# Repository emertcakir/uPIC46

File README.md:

# uPIC46
EMC

uPIC46 Development Board

The uPIC46 is a development board designed around the Microchip PIC18F46K22-I/PT microcontroller.  
It is intended for hobbyists, students, and professionals who want a versatile platform for learning, prototyping, and industrial communication testing.

----------------------------------------------------
✨ Features
----------------------------------------------------
- MCU: PIC18F46K22-I/PT (TQFP package)
- Clocking: External crystal oscillator support
- Memory Expansion: Onboard 24LC256 I²C EEPROM
- RTC: DS3231MZ real-time clock
- USB-UART Bridge: For programming and PC communication
- Connectivity:
  * UART, SPI, I²C headers exposed
  * RTS/CTS and other flow-control pins available on headers
  * RS-485 transceiver for half-duplex communication
  * CAN Bus interface via MCP2515 + SN65HVD230
- Reset & Indicators:
  * Reset push button
  * User indicator LEDs
- Headers:
  * Clearly labeled header pins (A1, A2, A3…) with silkscreen reference table on PCB
  * Breakout headers for easy access to MCU I/O pins

----------------------------------------------------
🛠 Hardware Design
----------------------------------------------------
- Compact and user-friendly layout
- Industrial interfaces: CAN and RS-485 included
- Silkscreen pinout table on PCB for quick reference
----------------------------------------------------
📸 Images
----------------------------------------------------

----------------------------------------------------
📜 License
----------------------------------------------------
This project is open-source. You are free to use, modify, and distribute it under the terms of the MIT License.

CRITICAL WARNING: This PCB design is currently an experimental, unverified prototype (AS-IS). I have not yet manufactured or functionally tested this version. Proceeding with production carries a high risk of failure and is undertaken solely at your own risk.

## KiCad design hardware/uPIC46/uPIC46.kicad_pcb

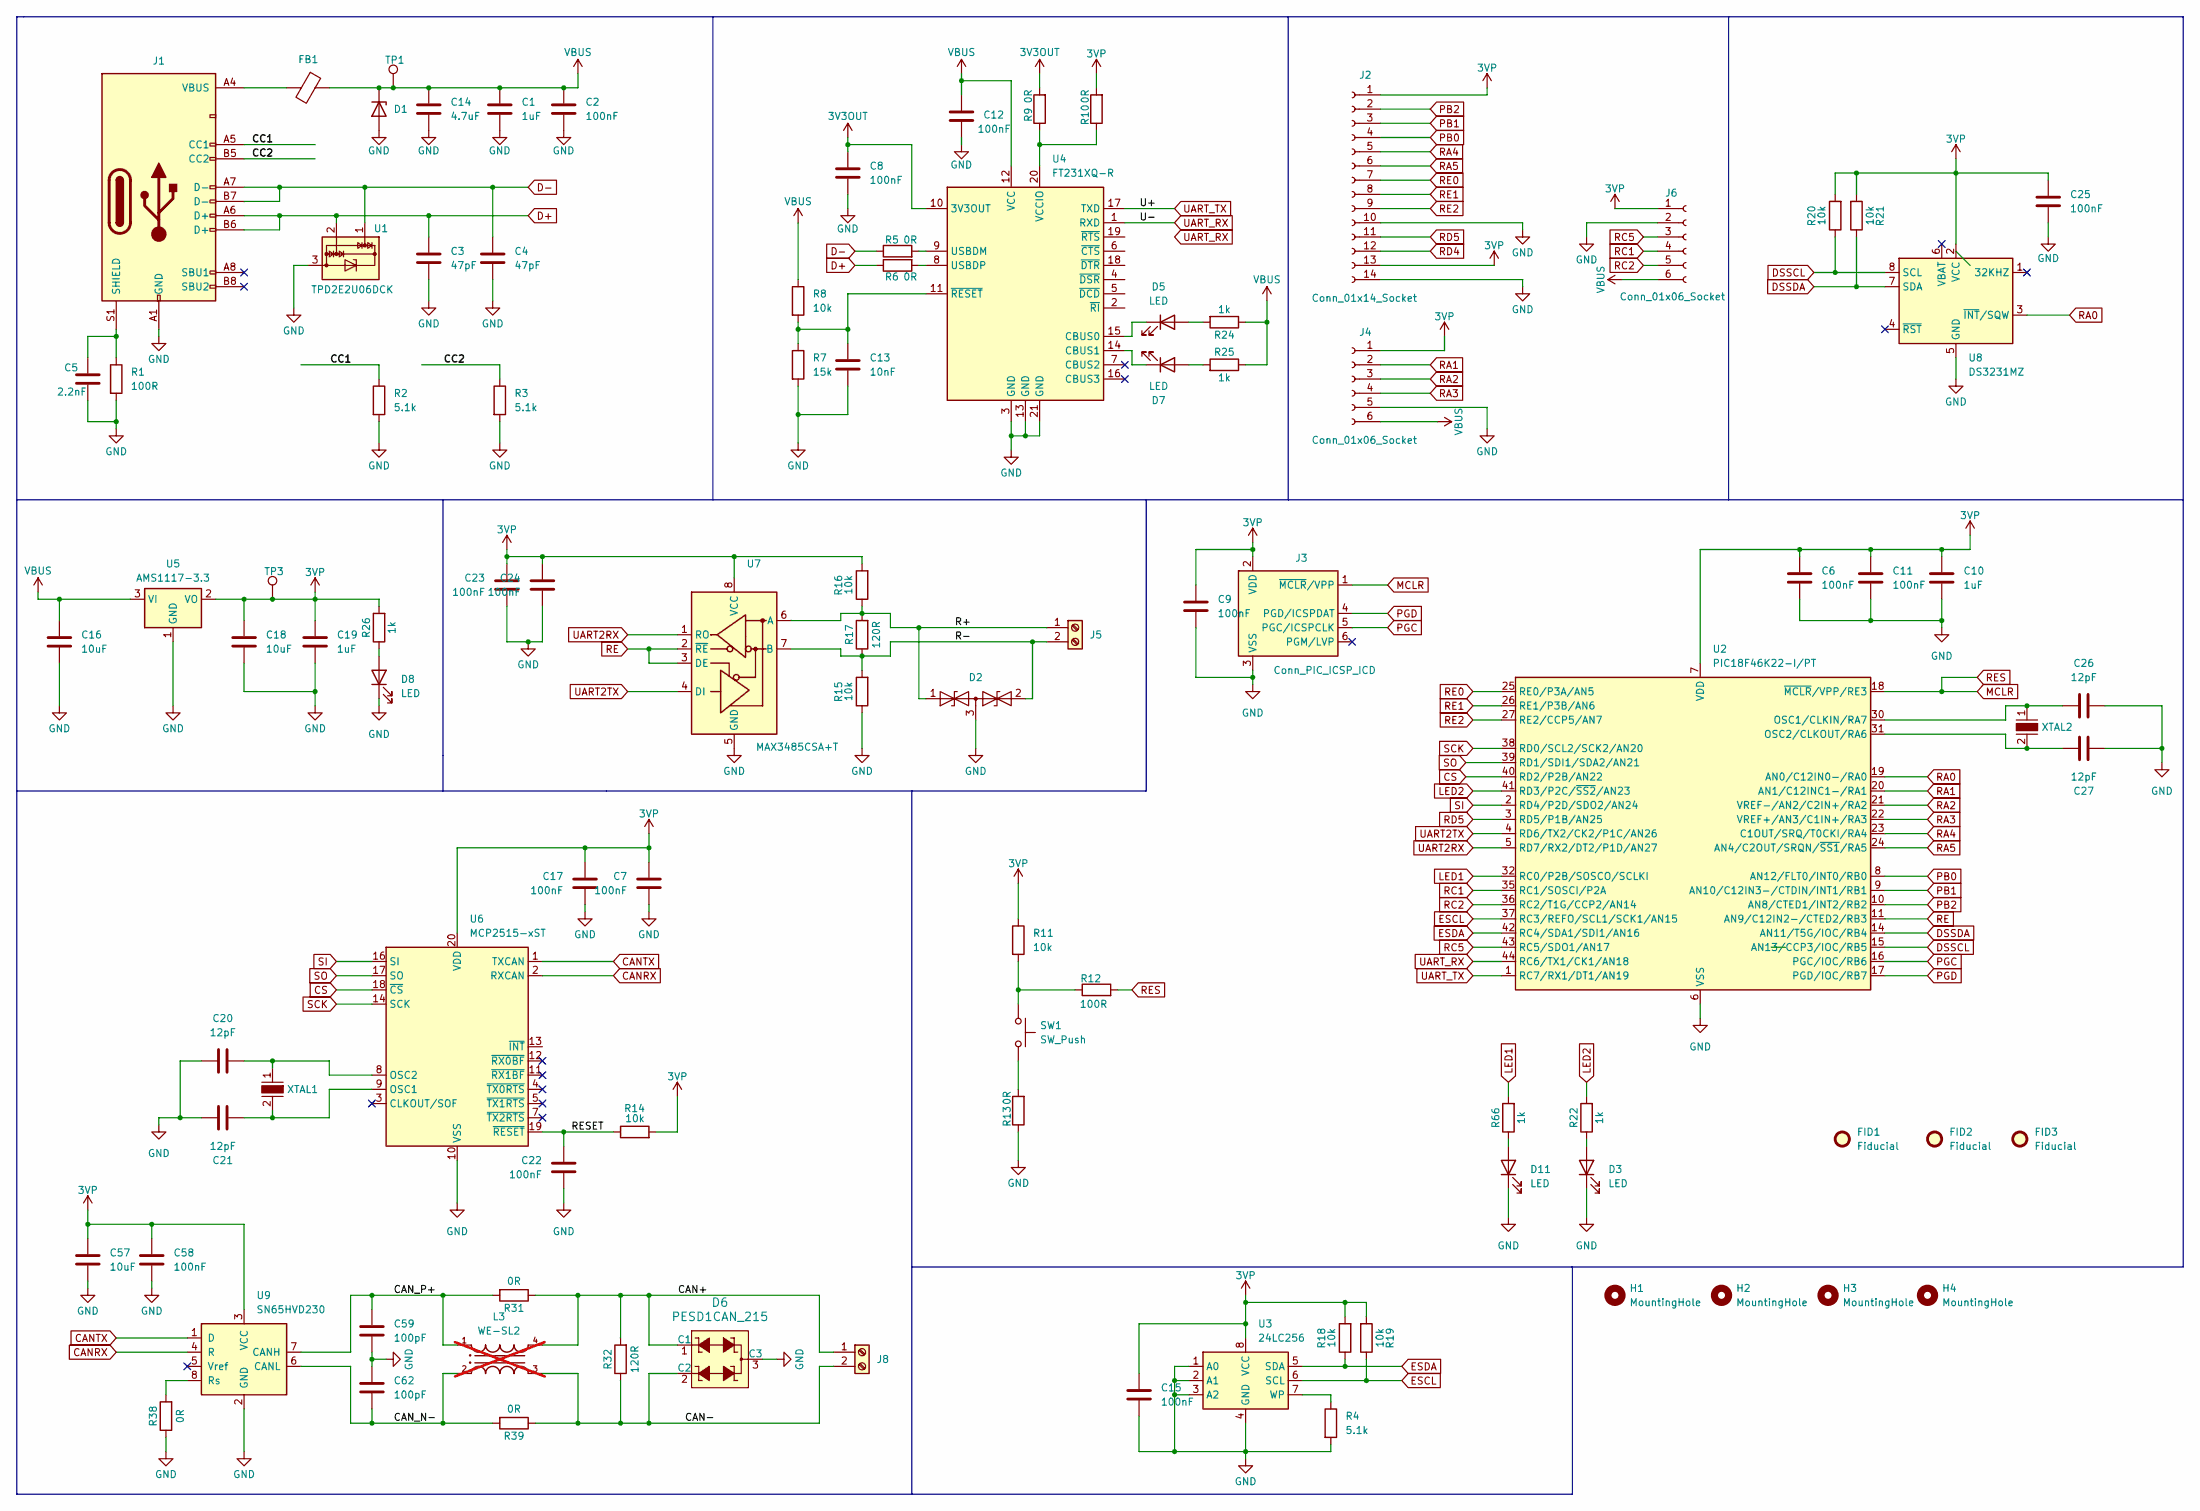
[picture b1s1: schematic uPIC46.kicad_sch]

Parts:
C1, C10, C19: 1uF; C_1206_3216Metric
C2, C6, C7, C8, C9, C11, C12, C15, C17, C22, C23, C24, C25, C58: 100nF; C_0603_1608Metric
C3, C4: 47pF; C_0603_1608Metric
C5: 2.2nF; C_0805_2012Metric
C13: 10nF; C_0603_1608Metric
C14: 4.7uF; C_1206_3216Metric
C16, C18, C57: 10uF; C_1206_3216Metric
C20, C21, C26, C27: 12pF; C_0603_1608Metric
C59, C62: 100pF; C_0603_1608Metric
D1: PTVS5V0Z1USKYL; Nexperia_DSN1608-2_1.6x0.8mm
D2: SM712_SOT23; SOT-23
D3, D5, D7, D8, D11: LED; LED_0603_1608Metric
D6: PESD1CAN_215; SOT-23-3; MPN PESD1CAN,215; Digi-Key_PN 1727-3817-1-ND
FB1: FerriteBead; L_0603_1608Metric
FID1, FID2, FID3: Fiducial; Fiducial_0.5mm_Mask1.5mm
H1, H2, H3, H4: MountingHole; MountingHole_3.2mm_M3_ISO7380
J1: USB_C_Receptacle_USB2.0_16P; USB_C_Receptacle_GCT_USB4110
J2: Conn_01x14_Socket; PinHeader_1x14_P2.54mm_Vertical
J3: Conn_PIC_ICSP_ICD; PinHeader_1x06_P2.54mm_Vertical
J4, J6: Conn_01x06_Socket; PinHeader_1x06_P2.54mm_Vertical
J5, J8: Screw_Terminal_01x02; TerminalBlock_RND_205-00045_1x02_P5.00mm_Horizontal
L3: WE-SL2; not fitted
R1, R12: 100R; R_0603_1608Metric
R2, R3, R4: 5.1k; R_0603_1608Metric
R5, R6, R9, R10, R13, R31, R38, R39: 0R; R_0603_1608Metric
R7: 15k; R_0603_1608Metric
R8, R11, R14, R15, R16, R18, R19, R20, R21: 10k; R_0603_1608Metric
R17, R32: 120R; R_0603_1608Metric
R22, R24, R25, R26, R66: 1k; R_0603_1608Metric
SW1: SW_Push; SW_SPST_EVQP2
TP1, TP3: TestPoint; TestPoint_Pad_D1.0mm
U1: TPD2E2U06DCK; SOT-323_SC-70
U2: PIC18F46K22-I/PT; TQFP-44_10x10mm_P0.8mm
U3: 24LC256; SOIC-8_3.9x4.9mm_P1.27mm
U4: FT231XQ-R; QFN-20-1EP_4x4mm_P0.5mm_EP2.5x2.5mm
U5: AMS1117-3.3; SOT-223-3_TabPin2
U6: MCP2515-xST; TSSOP-20_4.4x6.5mm_P0.65mm
U7: MAX3485CSA+T; SOIC-8_3.9x4.9mm_P1.27mm
U8: DS3231MZ; SOIC-8_3.9x4.9mm_P1.27mm
U9: SN65HVD230; SOIC-8_3.9x4.9mm_P1.27mm
XTAL1: NX3225GD-8MHZ-STD-CRA-3; SMD-2_3.2x2.5mm; MPN NX3225GD-8MHZ-STD-CRA-3; Digi-Key_PN 644-1178-1-ND
XTAL2: ECS-.327-12.5-34B-TR; SMD-2_3.2x1.5mm; MPN ECS-.327-12.5-34B-TR; Digi-Key_PN XC1617CT-ND

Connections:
3V3OUT: C8.1, R9.2, U4.10 (3V3OUT)
3VP: C6.1, C7.1, C9.1, C10.1, C11.1, C15.1, C17.1, C18.1, C19.1, C23.1, C24.1, C25.1, C57.1, C58.1, J2.1, J2.13, J3.2 (VDD), J4.1, J6.1, R10.2, R11.1, R14.2, R16.2, R18.2, R19.2, R20.2, R21.2, R26.2, TP3.1, U2.7 (VDD), U2.28 (VDD), U3.8 (VCC), U5.2 (VO), U6.20 (VDD), U7.8 (VCC), U8.2 (VCC), U9.3 (VCC)
/CAN+: D6.1 (C1), J8.1, L3.4, R31.1, R32.2
/CAN-: D6.2 (C2), J8.2, L3.3, R32.1, R39.1
/CAN_N-: C62.2, L3.2, R39.2, U9.6 (CANL)
/CAN_P+: C59.1, L3.1, R31.2, U9.7 (CANH)
/CC1: J1.A5 (CC1), R2.1
/CC2: J1.B5 (CC2), R3.1
/R+: D2.1 (A1), J5.1, R16.1, R17.2, U7.6 (A)
/R-: D2.2 (A2), J5.2, R15.2, R17.1, U7.7 (B)
/RESET: C22.1, R14.1, U6.19 (~RESET)
CANRX: U6.2 (RXCAN), U9.4 (R)
CANTX: U6.1 (TXCAN), U9.1 (D)
CS: U2.40 (RD2/P2B/AN22), U6.18 (~CS)
D+: C3.1, J1.A6 (D+), J1.B6 (D+), R6.1, U1.2
D-: C4.1, J1.A7 (D-), J1.B7 (D-), R5.1, U1.1
DSSCL: R20.1, U2.15 (AN13/CCP3/IOC/RB5), U8.8 (SCL)
DSSDA: R21.1, U2.14 (AN11/T5G/IOC/RB4), U8.7 (SDA)
ESCL: R19.1, U2.37 (RC3/REFO/SCL1/SCK1/AN15), U3.6 (SCL)
ESDA: R18.1, U2.42 (RC4/SDA1/SDI1/AN16), U3.5 (SDA)
GND: C1.2, C2.2, C3.2, C4.2, C5.2, C6.2, C7.2, C8.2, C9.2, C10.2, C11.2, C12.2, C13.2, C14.2, C15.2, C16.2, C17.2, C18.2, C19.2, C20.1, C21.1, C22.2, C23.2, C24.2, C25.2, C26.2, C27.2, C57.2, C58.2, C59.2, C62.1, D1.2 (A), D2.3 (common), D3.1 (K), D6.3 (C3), D8.1 (K), D11.1 (K), J1.A1 (GND), J1.A12 (GND), J1.B1 (GND), J1.B12 (GND), J2.10, J2.14, J3.3 (VSS), J4.5, J6.2, R1.2, R2.2, R3.2, R4.2, R7.2, R13.1, R15.1, R38.1, U1.3, U2.6 (VSS), U2.29 (VSS), U3.1 (A0), U3.2 (A1), U3.3 (A2), U3.4 (GND), U4.3 (GND), U4.13 (GND), U4.21 (GND), U5.1 (GND), U6.10 (VSS), U7.5 (GND), U8.5 (GND), U9.2 (GND)
LED1: R66.2, U2.32 (RC0/P2B/SOSCO/SCLKI)
LED2: R22.2, U2.41 (RD3/P2C/~SS2/AN23)
MCLR: J3.1 (~MCLR/VPP), R12.2, U2.18 (~MCLR/VPP/RE3)
unnamed: D3.2 (A), R22.1
unnamed: D5.2 (A), R24.2
unnamed: D5.1 (K), U4.15 (CBUS0)
unnamed: D7.2 (A), R25.2
unnamed: D7.1 (K), U4.14 (CBUS1)
unnamed: D8.2 (A), R26.1
unnamed: D11.2 (A), R66.1
unnamed: FB1.2, J1.A4 (VBUS), J1.A9 (VBUS), J1.B4 (VBUS), J1.B9 (VBUS)
unnamed: C5.1, J1.S1 (SHIELD), R1.1
unnamed: R11.2, R12.1, SW1.1
unnamed: R13.2, SW1.2
unnamed: C26.1, U2.30 (OSC1/CLKIN/RA7), XTAL2.1
unnamed: C27.1, U2.31 (OSC2/CLKOUT/RA6), XTAL2.2
unnamed: R4.1, U3.7 (WP)
unnamed: R5.2, U4.9 (USBDM)
unnamed: R6.2, U4.8 (USBDP)
unnamed: R9.1, R10.1, U4.20 (VCCIO)
unnamed: C13.1, R7.1, R8.2, U4.11 (~RESET)
unnamed: C21.2, U6.9 (OSC1), XTAL1.2
unnamed: C20.2, U6.8 (OSC2), XTAL1.1
unnamed: R38.2, U9.8 (Rs)
PB0: J2.4, U2.8 (AN12/FLT0/INT0/RB0)
PB1: J2.3, U2.9 (AN10/C12IN3-/CTDIN/INT1/RB1)
PB2: J2.2, U2.10 (AN8/CTED1/INT2/RB2)
PGC: J3.5 (PGC/ICSPCLK), U2.16 (PGC/IOC/RB6)
PGD: J3.4 (PGD/ICSPDAT), U2.17 (PGD/IOC/RB7)
RA0: U2.19 (AN0/C12IN0-/RA0), U8.3 (~INT/SQW)
RA1: J4.2, U2.20 (AN1/C12INC1-/RA1)
RA2: J4.3, U2.21 (VREF-/AN2/C2IN+/RA2)
RA3: J4.4, U2.22 (VREF+/AN3/C1IN+/RA3)
RA4: J2.5, U2.23 (C1OUT/SRQ/T0CKI/RA4)
RA5: J2.6, U2.24 (AN4/C2OUT/SRQN/~SS1/RA5)
RC1: J6.4, U2.35 (RC1/SOSCI/P2A)
RC2: J6.5, U2.36 (RC2/T1G/CCP2/AN14)
RC5: J6.3, U2.43 (RC5/SDO1/AN17)
RD4: J2.12
RD5: J2.11, U2.3 (RD5/P1B/AN25)
RE0: J2.7, U2.25 (RE0/P3A/AN5)
RE1: J2.8, U2.26 (RE1/P3B/AN6)
RE2: J2.9, U2.27 (RE2/CCP5/AN7)
RE: U2.11 (AN9/C12IN2-/CTED2/RB3), U7.2 (~RE), U7.3 (DE)
SCK: U2.38 (RD0/SCL2/SCK2/AN20), U6.14 (SCK)
SI: U2.2 (RD4/P2D/SDO2/AN24), U6.16 (SI)
SO: U2.39 (RD1/SDI1/SDA2/AN21), U6.17 (SO)
UART2RX: U2.5 (RD7/RX2/DT2/P1D/AN27), U7.1 (RO)
UART2TX: U2.4 (RD6/TX2/CK2/P1C/AN26), U7.4 (DI)
UART_RX: U2.44 (RC6/TX1/CK1/AN18), U4.1 (RXD)
UART_TX: U2.1 (RC7/RX1/DT1/AN19), U4.17 (TXD)
VBUS: C1.1, C2.1, C12.1, C14.1, C16.1, D1.1 (K), FB1.1, J4.6, J6.6, R8.1, R24.1, R25.1, TP1.1, U4.12 (VCC), U5.3 (VI)

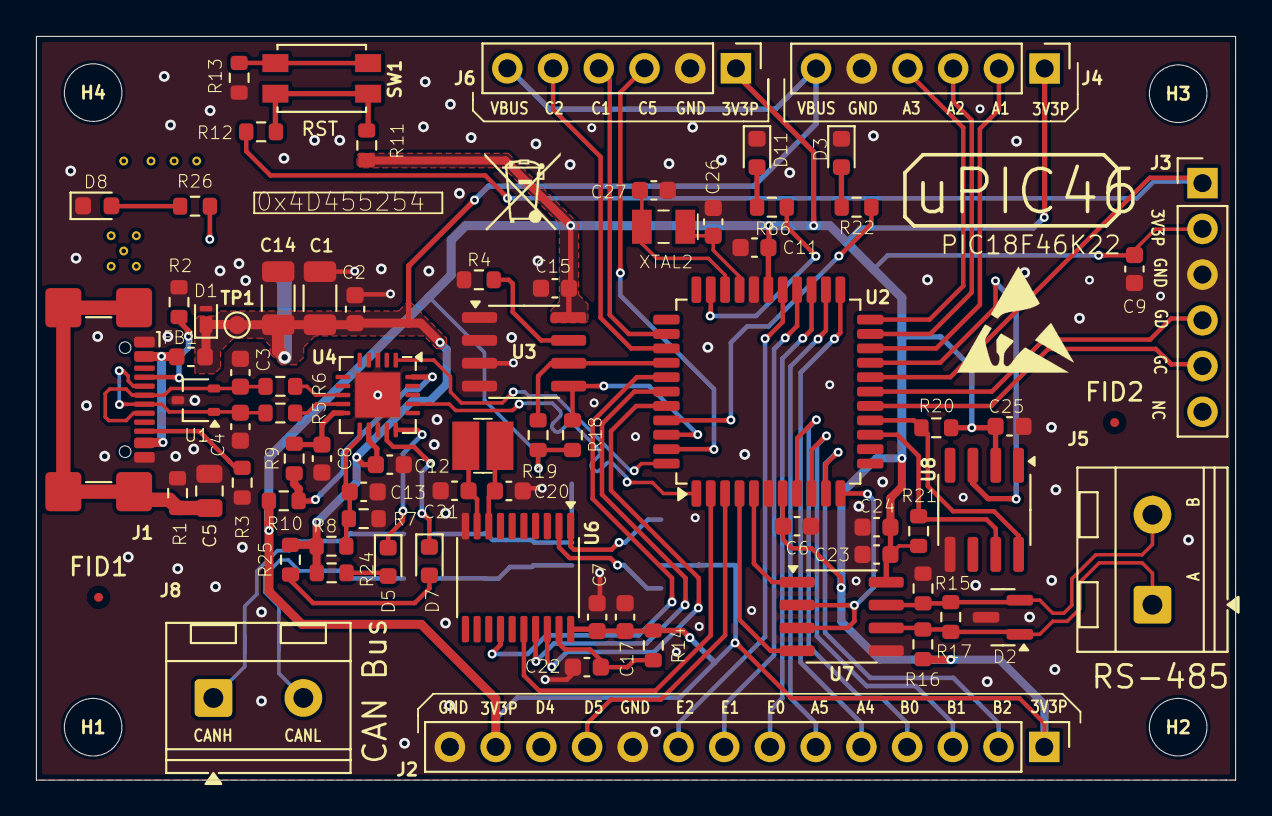
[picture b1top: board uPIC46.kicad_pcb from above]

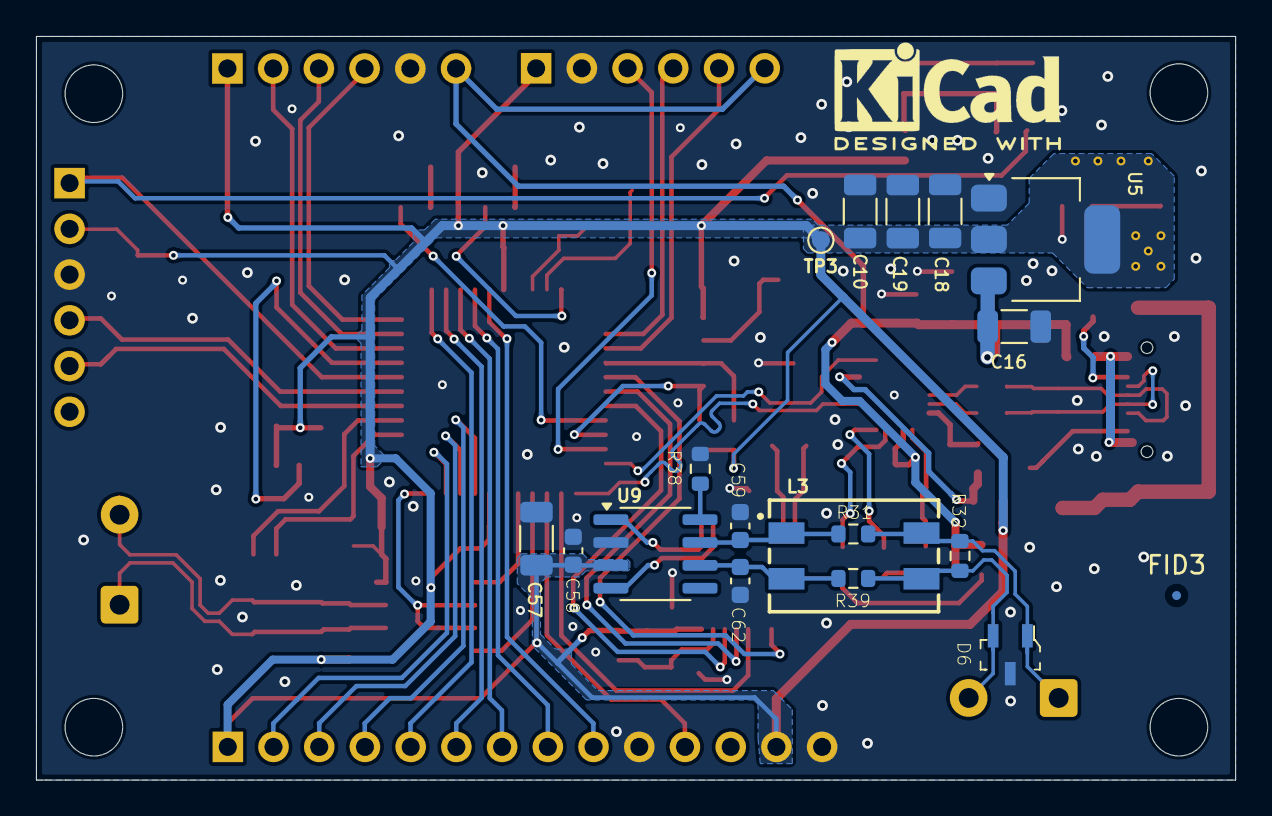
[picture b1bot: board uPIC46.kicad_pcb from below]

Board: 2 copper layers, 66.6 x 41.3 mm, 99 parts (18 on the bottom side), 72 nets.

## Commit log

2025-09-19 designators
